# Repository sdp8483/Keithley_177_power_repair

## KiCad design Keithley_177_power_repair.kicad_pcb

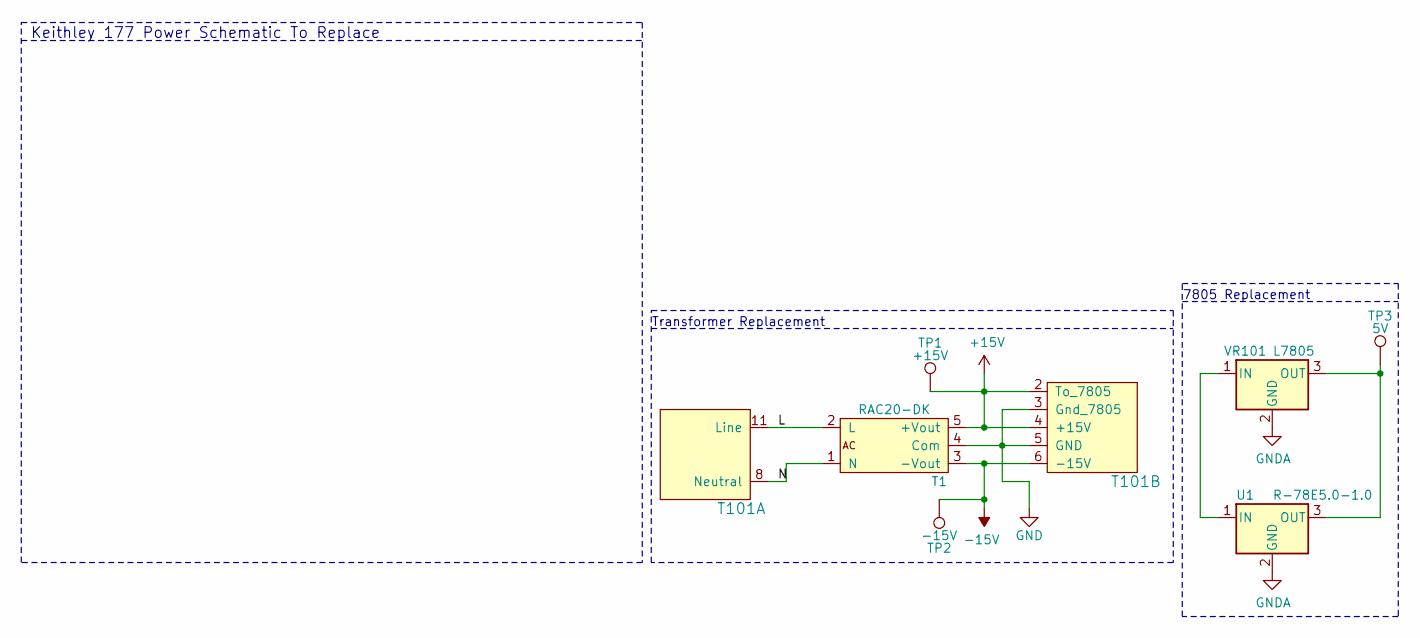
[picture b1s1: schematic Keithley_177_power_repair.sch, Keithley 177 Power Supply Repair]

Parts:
T1: RAC20-DK; RAC20-K
T101: Transformer; Keithley_Transformer
TP1: +15V; TestPoint_Pad_D2.0mm
TP2: -15V; TestPoint_Pad_D2.0mm
TP3: 5V; TestPoint_Pad_D2.0mm
U1: R-78E5.0-1.0; Converter_DCDC_RECOM_R-78E-0.5_THT
VR101: L7805; Voltage_Regulator

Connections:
+15V: T1.5 (+Vout), T101.2 (To_7805), T101.4 (+15V), TP1.1
-15V: T1.3 (-Vout), T101.6 (-15V), TP2.1
/L: T1.2 (L), T101.11 (Line)
/N: T1.1 (N), T101.8 (Neutral)
GND: T1.4 (Com), T101.3 (Gnd_7805), T101.5 (GND)
GNDA: U1.2 (GND), VR101.2 (GND)
unnamed: TP3.1, U1.3 (OUT), VR101.3 (OUT)
unnamed: U1.1 (IN), VR101.1 (IN)

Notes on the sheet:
Keithley 177 Power Schematic To Replace
7805 Replacement
Transformer Replacement

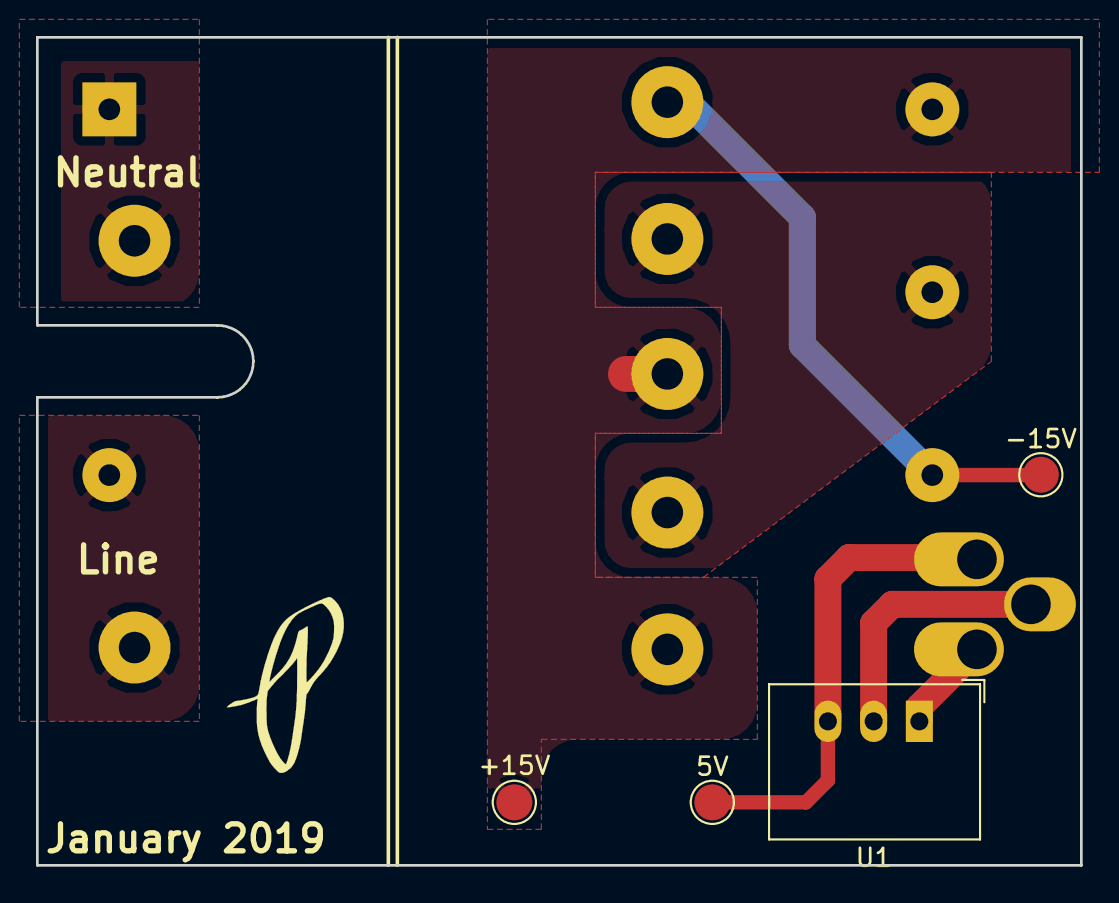
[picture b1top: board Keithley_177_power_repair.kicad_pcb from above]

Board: 2 copper layers, 58.0 x 46.0 mm, 7 parts (0 on the bottom side), 8 nets.

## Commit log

2019-01-15 create custom symbol
2019-01-15 initial schematic
2019-01-15 start footprint
2019-01-16 spell check transformer
2019-01-16 create footprint
2019-01-16 remove unused pins
2019-01-16 assign footprints
2019-01-16 add edge cuts
2019-01-19 Update dimensions based on BigPrint Measurments
2019-01-19 update dims from BigPrint measurements
2019-01-19 remove links
2019-01-19 remove silkscreen outline
2019-01-19 update page size and title block
2019-01-19 output SVG for printing
2019-01-19 increase drill diameters
2019-01-19 modify for larger drill holes
2019-01-19 reduce pin 2 length
2019-01-19 update footprints
2019-01-19 add 3d model
2019-01-19 ignore FCStd1 files
2019-01-19 save after KiCad StepUp
2019-01-20 save after export to kicad
2019-01-20 add Vreg 3d model
2019-01-20 generate gerbers
2019-01-20 add images of jumer locatins on main PCB
